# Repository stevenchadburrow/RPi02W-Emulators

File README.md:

# RPi02W-Emulators
<b>Running Emulators on a Raspberry Pi Zero 2W</b><br>

<b>Purpose:</b><br>
This project is to introduce myself to how the Raspberry Pi Zero 2W works, and further my knowledge on 'modern' microprocessors running Linux.  The immediate goal is to make a handheld device that plays NES, Gameboy, Gameboy Color, and Gameboy Advance games that can also connect to the television.  Additional emulators to follow.<br>

<b>Connecting an ILI9341 LCD in SPI mode using pins:</b><br>
CS = GPIO8 / Pin24<br>
MISO = GPIO9 / Pin21<br>
MOSI = GPIO10 / Pin19<br>
SCLK = GPIO11 / Pin23<br>
RESET = GPIO0 / Pin27<br>
DC = GPIO1 / Pin28<br>
LED is connected to 3V3<br>

<b>Connecting a 3.5mm Audio Jack using pins:</b><br>
LEFT = GPIO12 / Pin32<br>
RIGHT = GPIO13 / Pin33<br>

<b>Additional Requirements:</b><br>
You will also need a USB-Micro to USB-A (Female) adapter, and an HDMI-mini to HDMI adapter.<br>

<b>Instructions to Install:</b><br>
1) Re-image an 8GB+ SD Card with Raspberry Pi OS (Lite) 64-bit.<br>
2) Create user named ``` username ``` with pass named ``` password ```.<br>
3) ``` sudo raspi-config ```, change settings in Auto Login to automatically login without password required, as well as booting to Console instead of Desktop.<br>
4) ``` mkdir ~/Emulators ```, put all files found here into that folder.<br>
5) ``` mkdir ~/Emulators/ROMS ```, put whatever ROMs into that folder.  You can use sub-folders to help organize your ROMs.<br>
6) You can pull the SD Card from the Pi and connect it to another Linux computer to transfer files, use built-in Desktop environment, or some other means.<br>
7) ``` sudo nano /boot/firmware/config.txt ```, and comment out the line ``` #dtoverlay=vc4-kms-v3d ```, the then add these lines to the bottom under ``` [all] ```:
   ```
   dtoverlay=vc4-fkms-v3d
   hdmi_group=1
   hdmi_mode=1
   hdmi_drive=2
   max_framebuffers=2
   enable_tvout=0
   dtparam=spi=on
   dtoverlay=fbtft,spi0-0,ili9341,bgr,rotate=270,speed=50000000,dc_pin=1,reset_pin=0,framebuffer_width=320,framebuffer_height=240
   dtoverlay=audremap,pins_12_13
   audio_pwm_mode=2
   disable_audio_dither
   ```
8) Optionally you can also overclock the Pi by also including:
   ```
   arm_freq=1200
   over_voltage=2
   ```
9) ``` sudo nano /boot/firmware/cmdline.txt ```, then add to the end of the first line:
   ```
   video=HDMI-A-1:640x480M@60,margin_top=20,margin_bottom=20,margin_left=20,margin_right=20
   ```
10) ``` sudo nano /etc/rc.local ```, and if file already exists, just add ``` sudo modprobe snd-pcm-oss ```.  Else, add these lines to the file:
    ```
    #!/bin/sh
    sudo modprobe snd-pcm-oss
    exit 0
    ```
11) ``` sudo chmod +rwx /etc/rc.local ; sudo chown root /etc/rc.local ``` to give permissions to file.<br>
12) ``` sudo reboot ``` for changes to take effect.<br>
13) ``` cd ~/Emulators ; sh install.sh ```, to compile all C files.<br>
14) To run: ``` cd ~/Emulators ; sh run.sh ```, or to auto run on boot: ``` echo 'cd ~/Emulators/ ; sh run.sh' >> ~/.bashrc ```.<br>

<b>Features:</b><br>
- If HDMI is plugged in on boot, games will be played through HDMI.  Else, games will be played through LCD.<br>
- It can use the on-board buttons, a USB keyboard, or an Xbox360 style USB controller.<br>
- Has additional features such as fast-forward button, turbo buttons, and save/load RAM to external file.<br>
- All files here are compiled using ``` gcc ``` and only uses standard Linux libraries.<br>
- In order to draw to the screen, each emulator will write directly to ``` /dev/fb0 ```.<br>
- In order to get on-board button state, each emulator will read directly from GPIO pins using the ``` pigpio ``` library.<br>
- In order to get keyboard events, each emulator will read directly from ``` /dev/input/event0 ```.<br>
- In order to get joystick events, each emulator will read directly from ``` /dev/input/js0 ```.<br>
- In order to send audio data, each emulator will stream directly to ``` /dev/dsp ```.<br>
- Warning: ``` /dev/dsp ``` is only available after ``` sudo modprobe snd-pcm-oss ```.<br>

<b>NES, GB, and GBA Emulator Development:</b><br>
- PICnes is my own NES emulator that was previously made for the PIC32MZ, initial code found <a href="https://github.com/stevenchadburrow/AcolyteHandheld">here</a>.<br>
- PeanutGB is an MIT licensed GB/GBC emulator, found <a href="https://github.com/deltabeard/Peanut-GB">here</a>. The PeanutGB emulator used is actually a version by 'froggestspirit', found <a href="https://github.com/froggestspirit/Peanut-GB">here</a>, in order to play Gameboy Color games.<br>
- gdkGBA is a public domain GBA emulator, found <a href="https://github.com/gdkchan/gdkGBA">here</a>.  I have been altering it by copying code from a version by 'jakibaki', found <a href="https://github.com/jakibaki/gdkGBA">here</a>.  It runs well enough at 20 FPS.  I'm using Normmatt's open-source BIOS, hosted by Nebuleon <a href="https://github.com/Nebuleon/ReGBA/">here</a>.<br>

<b>Videos:</b><br>
<a href="https://youtube.com/shorts/ARCSKjPH7FA?si=rqlXaKl9zKCdxzBo">Youtube Short of me playing Tobu Tobu Girl DX</a><br>

<b>Pictures:</b><br>
<br>
<br>
<br>
<br>
<br>

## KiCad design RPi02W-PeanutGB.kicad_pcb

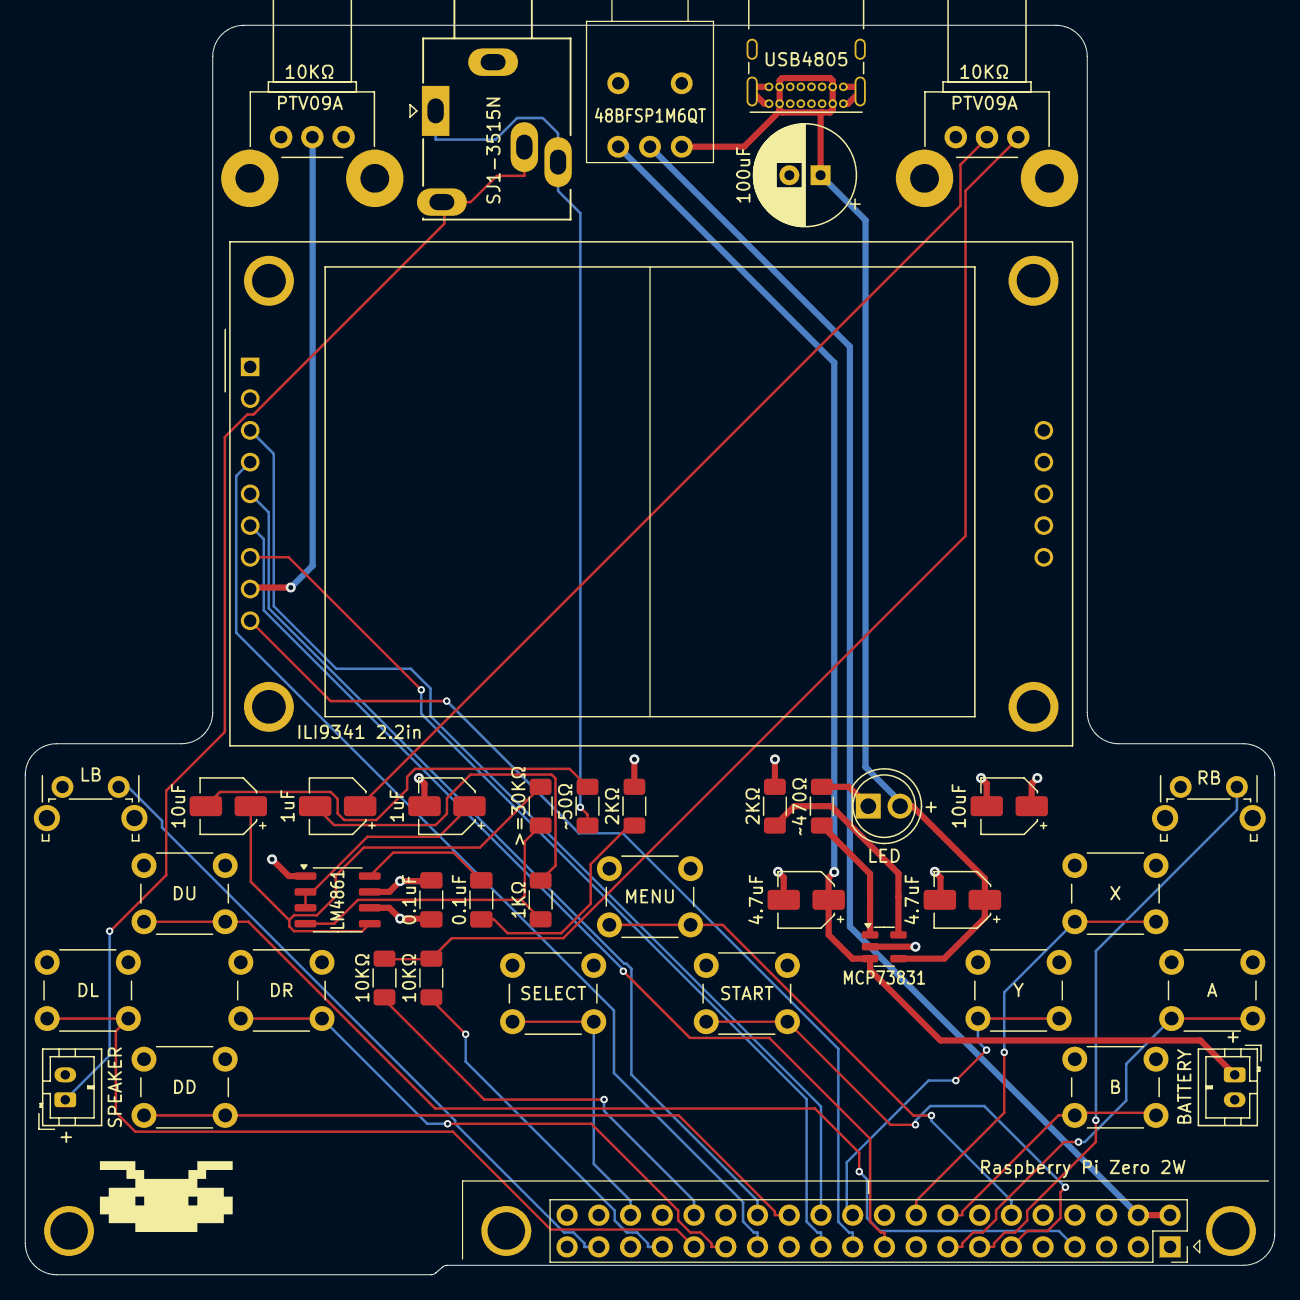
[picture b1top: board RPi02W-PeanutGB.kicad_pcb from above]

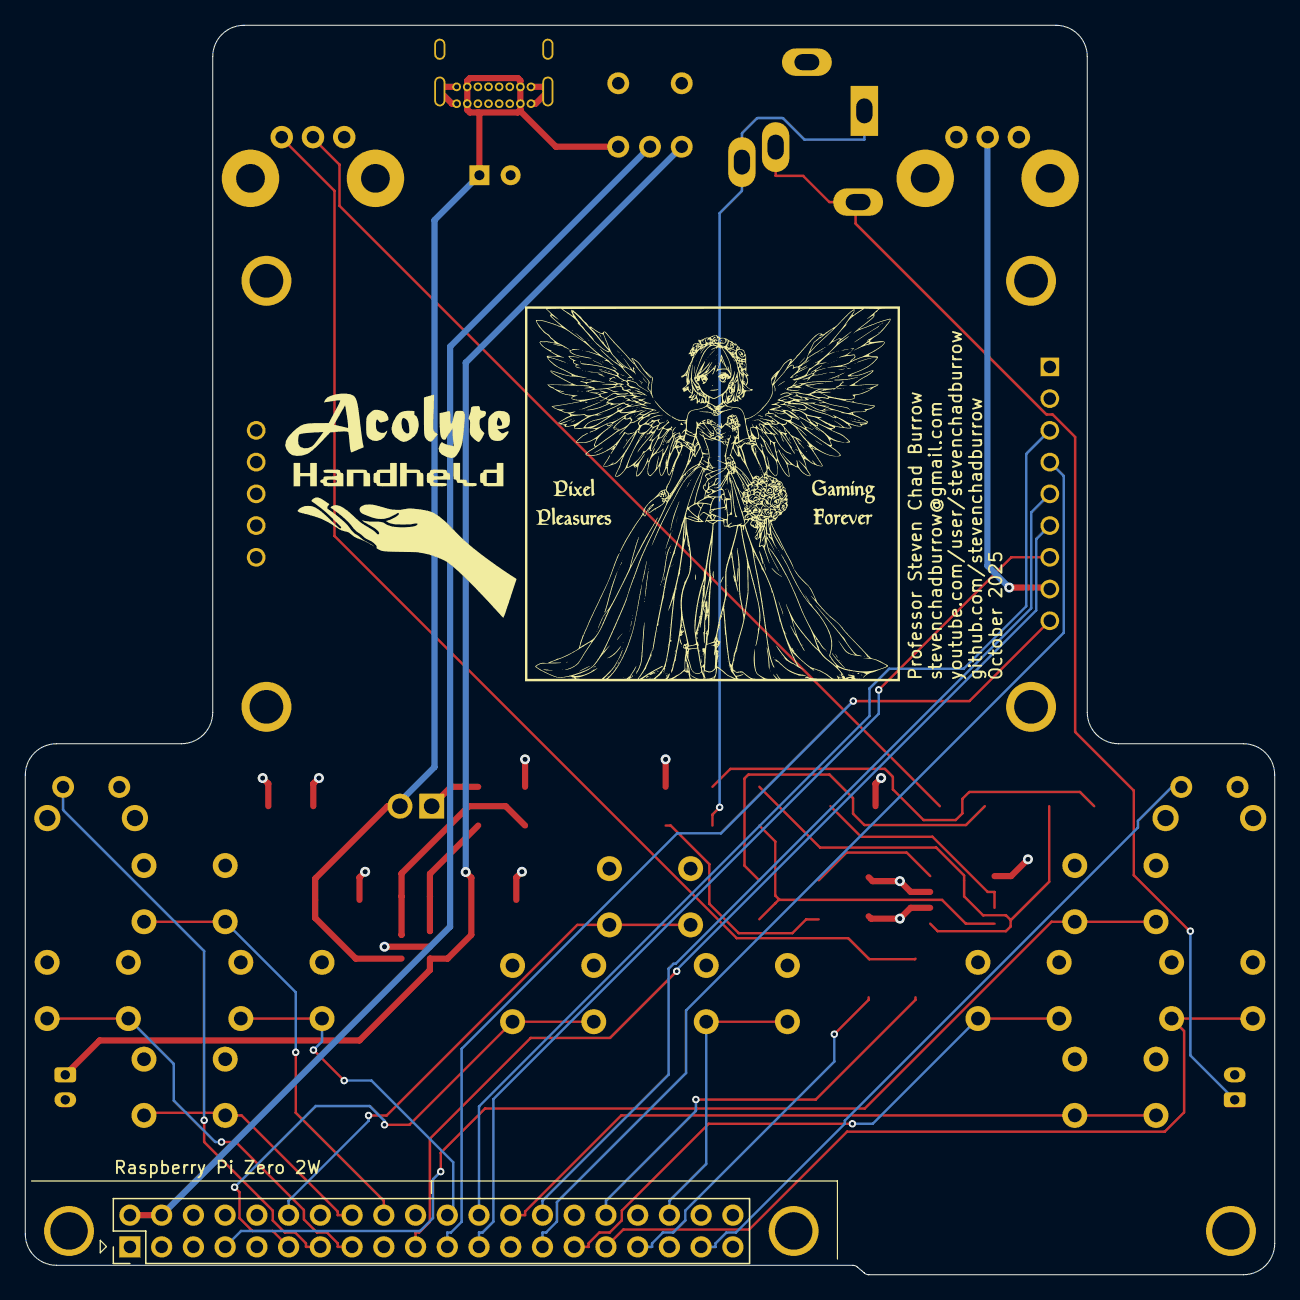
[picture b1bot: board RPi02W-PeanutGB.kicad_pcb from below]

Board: 4 copper layers, 100.0 x 100.0 mm, 50 parts (5 on the bottom side), 41 nets.

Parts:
BT1: Battery_Cell; JST_PH_B2B-PH-K_1x02_P2.00mm_Vertical
C1, C2, C3, C4, C5, C9: C_Polarized_Small_US; CP_Elec_4x5.8
C6, C7: C_Small; C_1206_3216Metric_Pad1.33x1.80mm_HandSolder
C8: C_Polarized_Small_US; CP_Radial_D8.0mm_P2.50mm
D1: LED; LED_Custom_D5.0mm
G100: LOGO; Angel
G101: LOGO; Acolyte
G102: LOGO; Handheld
G103: LOGO; Hand
G109: LOGO; Alien
J1: Raspberry_Pi_2_3; PinHeader_2x20_P2.54mm_Vertical
J3: AudioJack3_SwitchTR; Jack_3.5mm_Ledino_Edited_KB3SPRS_Horizontal
J9: USB_C_Receptacle; USB_C_Receptacle_GCT_USB4085
LS1: Speaker; JST_PH_B2B-PH-K_1x02_P2.00mm_Vertical
R1, R2, R3, R4, R5, R6, R7, R8: R_US; R_1206_3216Metric_Pad1.30x1.75mm_HandSolder
RV2, RV3: R_Potentiometer_US; Potentiometer_Bourns_PTV09A-2_Single_Horizontal
SW1: SW_SPDT_MSM; 48BFSP1M6QT
SW2, SW3, SW4, SW5, SW6, SW7, SW8, SW9, SW12, SW13, SW14: SW_Push; SW_PUSH_6mm
SW10, SW11: SW_Push; SW_Tactile_SPST_Angled_PTS645Vx83-2LFS
TP1, TP2, TP3: TestPoint; ScrewHole-RPiZero
U1: MCP73831-2-OT; SOT-23-5
U3: LM4861MX; SO-8_3.9x4.9mm_P1.27mm
U4: CR2013-MI2120

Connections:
+3V3: C6.2, C9.1, J1.1 (3V3), J1.17 (3V3), RV3.1, U3.6 (VDD), U4.1 (VCC)
+3V8: BT1.1 (+), C2.1, SW1.1, U1.3 (V_{BAT})
+5V: C1.1, C8.1, D1.2 (A), J9.A4 (VBUS), J9.A9 (VBUS), J9.B4 (VBUS), J9.B9 (VBUS), SW1.3 (4), U1.4 (V_{DD})
AUDIO-LEFT: J1.32 (PWM0/GPIO12), R3.1
AUDIO-OUT: J3.R, J3.T, R7.1
AUDIO-RIGHT: J1.33 (PWM1/GPIO13), R4.2
AUDIO-SPEAKER: J3.RN, J3.TN, LS1.1
BUTTON-A: J1.15 (GPIO22), SW6.2
BUTTON-B: J1.16 (GPIO23), SW7.2
BUTTON-DD: J1.29 (GCLK1/GPIO5), SW3.2
BUTTON-DL: J1.31 (GCLK2/GPIO6), SW4.2
BUTTON-DR: J1.26 (~CE1/GPIO7), SW5.2
BUTTON-DU: J1.7 (GCLK0/GPIO4), SW2.2
BUTTON-LB: J1.37 (GPIO26), SW10.2
BUTTON-MENU: J1.12 (GPIO18/PWM0), SW14.2
BUTTON-RB: J1.13 (GPIO27), SW11.2
BUTTON-SELECT: J1.36 (GPIO16), SW12.2
BUTTON-START: J1.11 (GPIO17), SW13.2
BUTTON-X: J1.18 (GPIO24), SW8.2
BUTTON-Y: J1.22 (GPIO25), SW9.2
GND: BT1.2 (-), C1.2, C2.2, C4.2, C6.1, C8.2, C9.2, J1.6 (GND), J1.9 (GND), J1.14 (GND), J1.20 (GND), J1.25 (GND), J1.30 (GND), J1.34 (GND), J1.39 (GND), J3.S, J9.A1 (GND), J9.A12 (GND), J9.B1 (GND), J9.B12 (GND), J9.S1 (SHIELD), LS1.2, R1.2, R8.1, RV2.3, RV3.3, SW2.1, SW3.1, SW4.1, SW5.1, SW6.1, SW7.1, SW8.1, SW9.1, SW10.1, SW11.1, SW12.1, SW13.1, SW14.1, TP1.1, TP2.1, TP3.1, U1.2 (V_{SS}), U3.1 (SD), U3.7 (GND), U4.2 (GND)
LCD-BL: RV3.2, U4.8 (LED)
LCD-CS: J1.24 (~CE0/GPIO8), U4.3 (~CS)
LCD-DC: J1.28 (ID_SC/GPIO1), U4.5 (D/~C)
LCD-MISO: J1.21 (MISO0/GPIO9), U4.9 (MISO)
LCD-MOSI: J1.19 (MOSI0/GPIO10), U4.6 (MOSI)
LCD-RESET: J1.27 (ID_SD/GPIO0), U4.4 (RESET)
LCD-SCLK: J1.23 (SCLK0/GPIO11), U4.7 (SCK)
unnamed: C3.1, RV2.2
unnamed: C3.2, R5.2
unnamed: C5.2, R7.2
unnamed: C7.1, R8.2
unnamed: D1.1 (K), R2.1
unnamed: R3.2, R4.1, RV2.1
unnamed: R1.1, U1.5 (PROG)
unnamed: C4.1, U3.2 (BYPASS), U3.3 (+IN)
unnamed: R5.1, R6.2, U3.4 (-IN)
unnamed: C5.1, R6.1, U3.5 (VO1)
unnamed: C7.2, U3.8 (VO2)
POWER: J1.2 (5V), J1.4 (5V), SW1.2 (3)
STAT: R2.2, U1.1 (STAT)

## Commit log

2025-09-27 Rename RPi02W-PeanutGB-HDMI.jpg to RPi02W-PeanutGB-HDMI-Testing.jpg
2025-09-27 Rename RPi02W-PeanutGB-LCD.jpg to RPi02W-PeanutGB-LCD-Testing.jpg
2025-09-27 Rename RPi02W-PeanutGB-LCD-Testing.jpg to RPi02W-PeanutGB-LCD-Preliminary.jpg
2025-10-11 Rename install.sh to PeanutGB/install.sh
2025-10-11 Rename joystick.c to PeanutGB/joystick.c
2025-10-11 Rename keyboard.c to PeanutGB/keyboard.c
2025-10-11 Rename main.c to PeanutGB/main.c
2025-10-11 Rename menu.c to PeanutGB/menu.c
2025-10-11 Rename minigb_apu.c to PeanutGB/minigb_apu.c
2025-10-11 Rename peanut_gb.c to PeanutGB/peanut_gb.c
2025-10-11 Rename peanut_gbc.h to PeanutGB/peanut_gbc.h
2025-10-11 Rename minigb_apu.h to PeanutGB/minigb_apu.h
2025-10-11 Rename run.sh to PeanutGB/run.sh
2025-10-11 Update LICENSE
2025-10-16 Rename RPi02W-PeanutGB-Enclosure.scad to RPi02W-Emulators-Enclosure.scad
2025-10-16 Rename RPi02W-PeanutGB-Gerbers.zip to RPi02W-Emulators-Gerbers.zip
2025-10-16 Rename RPi02W-Emulators-Enclosure.scad to RPi02W-Enclosure.scad
2025-10-16 Rename RPi02W-PeanutGB-Schematics.pdf to RPi02W-Schematics.pdf
2025-10-16 Rename RPi02W-PeanutGB.kicad_pcb to RPi02W.kicad_pcb
2025-10-16 Rename RPi02W-PeanutGB.kicad_sch to RPi02W.kicad_sch
2025-10-17 Rename RPi02W-PeanutGB-Prelim-Case.png to RPi02W-Prelim-Case.png
2025-10-17 Rename RPi02W-PeanutGB-Prelim-PCB.png to RPi02W-Prelim-PCB.png
2025-10-17 Rename RPi02W-PeanutGB-Prelim-HDMI.jpg to RPi02W-Prelim-HDMI.jpg
2025-10-17 Rename RPi02W-PeanutGB-Prelim-LCD.jpg to RPi02W-Prelim-LCD.jpg
